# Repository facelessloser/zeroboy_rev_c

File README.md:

# zeroboy_rev_c
rev c of my zeroboy raspberry pi portable

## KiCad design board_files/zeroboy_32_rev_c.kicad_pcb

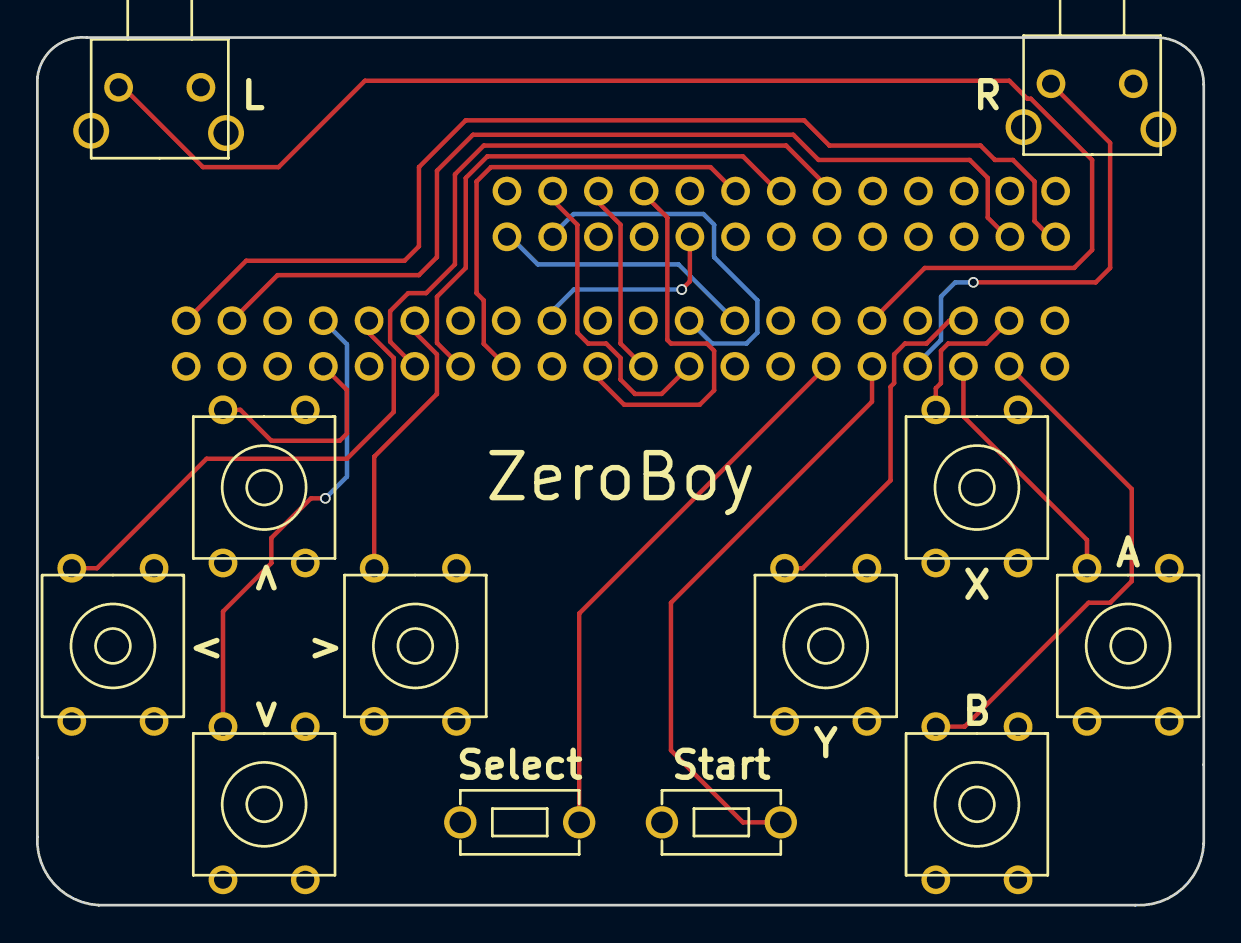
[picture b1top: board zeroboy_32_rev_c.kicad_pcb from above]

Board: 2 copper layers, 64.8 x 48.2 mm, 14 parts (0 on the bottom side), 24 nets.

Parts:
U1: RASPBERRY_PI_HEADER_26_pins; raspberry_pi_one_26pin_gpio_custom
U2, U4, U6, U7, U10, U12, U13, U14: push_button; button_soft_touch_custom
U3: RASPBERRY_PI_HEADER; raspberry_pi_gpio_custom
U5, U11: push_button; right_angle_button_custom
U8, U9: push_button; small_button_2pin_custom

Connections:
unnamed: U1.2, U3.2
unnamed: U1.4, U3.4
unnamed: U1.6, U2.2, U3.6, U4.2, U5.2, U6.2, U7.2, U8.2, U9.2, U10.2, U11.2, U12.2, U13.2, U14.2
unnamed: U1.11, U3.11
unnamed: U1.13, U3.13
unnamed: U1.15, U3.15
unnamed: U1.18, U3.18
unnamed: U1.19, U3.19
unnamed: U1.21, U3.21
unnamed: U1.23, U3.23
unnamed: U1.24, U3.24
unnamed: U1.26, U3.26
unnamed: U2.1, U3.7
unnamed: U3.29, U8.1
unnamed: U3.31, U9.1
unnamed: U3.32, U5.1
unnamed: U3.35, U7.1
unnamed: U3.36, U6.1
unnamed: U3.37, U4.1
unnamed: U3.12, U10.1
unnamed: U3.33, U11.1
unnamed: U3.38, U12.1
unnamed: U3.10, U13.1
unnamed: U3.8, U14.1

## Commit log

2018-04-14 board files
